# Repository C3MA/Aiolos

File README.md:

avr-template
============

A minimal template for AVR microcontroller projects. Usage:

1. Fork this repository, then rename it to reflect your project
(Admin->Rename on Github)
2. Clone your repository
3. Change the Makefile to reflect your microcontroller, programmer etc.

### License

The UART code is written by Peter Fleury. Everything else: BSD 2-clause
license as below:

Copyright (c) 2012, Mathias Dalheimer
All rights reserved.

Redistribution and use in source and binary forms, with or without
modification, are permitted provided that the following conditions are
met:

* Redistributions of source code must retain the above copyright notice, 
this list of conditions and the following disclaimer.

* Redistributions in binary form must reproduce the above copyright
notice, this list of conditions and the following disclaimer in the
documentation and/or other materials provided with the distribution.

THIS SOFTWARE IS PROVIDED BY THE COPYRIGHT HOLDERS AND CONTRIBUTORS "AS
IS" AND ANY EXPRESS OR IMPLIED WARRANTIES, INCLUDING, BUT NOT LIMITED
TO, THE IMPLIED WARRANTIES OF MERCHANTABILITY AND FITNESS FOR A
PARTICULAR PURPOSE ARE DISCLAIMED. IN NO EVENT SHALL THE COPYRIGHT
HOLDER OR CONTRIBUTORS BE LIABLE FOR ANY DIRECT, INDIRECT, INCIDENTAL,
SPECIAL, EXEMPLARY, OR CONSEQUENTIAL DAMAGES (INCLUDING, BUT NOT
LIMITED TO, PROCUREMENT OF SUBSTITUTE GOODS OR SERVICES; LOSS
OF USE, DATA, OR PROFITS; OR BUSINESS INTERRUPTION) HOWEVER
CAUSED AND ON ANY THEORY OF LIABILITY, WHETHER IN CONTRACT,
STRICT LIABILITY, OR TORT (INCLUDING NEGLIGENCE OR OTHERWISE)
ARISING IN ANY WAY OUT OF THE USE OF THIS SOFTWARE, EVEN IF ADVISED OF
THE POSSIBILITY OF SUCH DAMAGE.

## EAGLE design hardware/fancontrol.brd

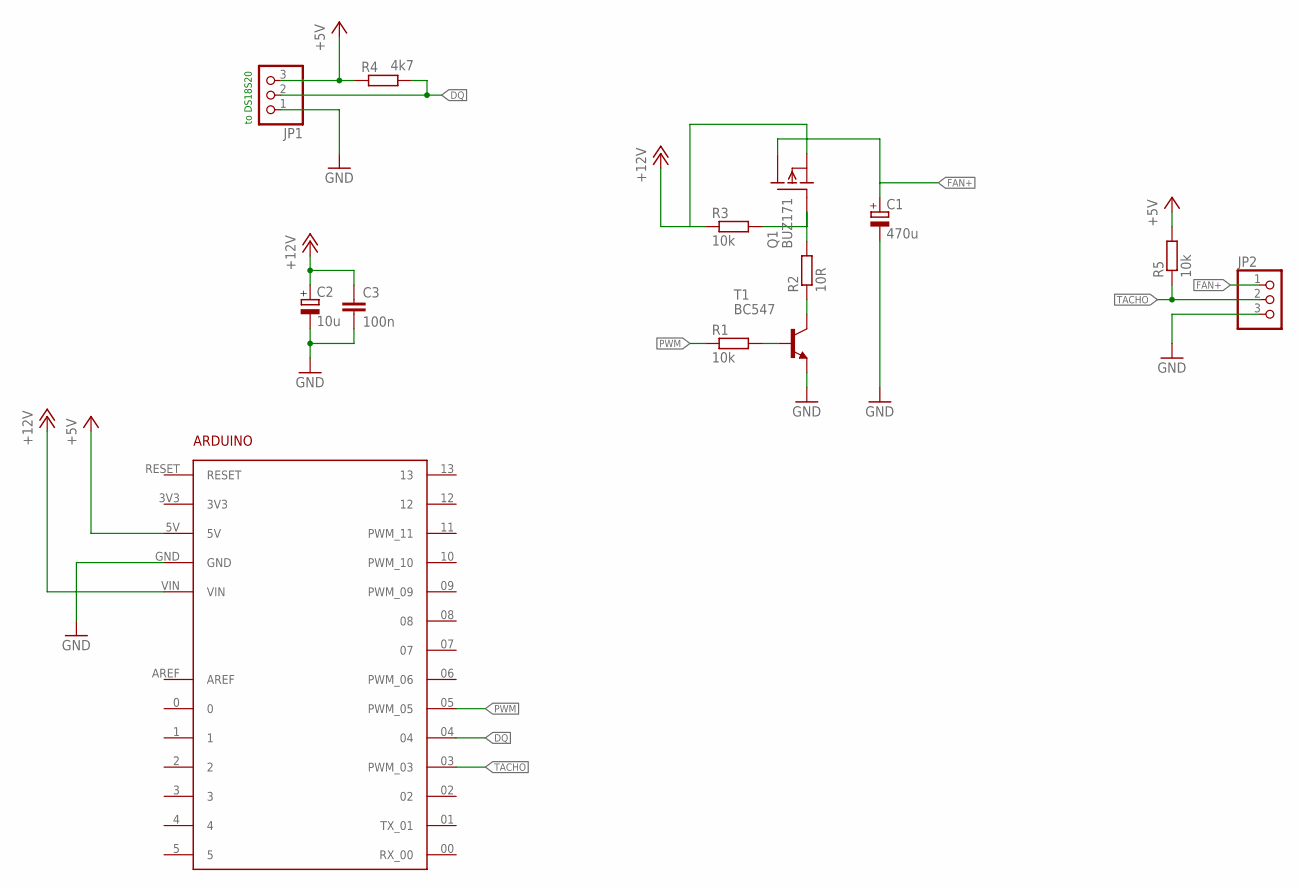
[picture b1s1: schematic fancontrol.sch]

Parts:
ARDUINO1: ARDUINO
C1: 470u; E5-10,5
C2: 10u; E2,5-5
C3: 100n; C025-025X050
JP1, JP2: PINHD-1X3; 1X03
Q1: BUZ171; TO220
R1, R3, R5: 10k; 0207/7
R2: 10R; 0207/7
R4: 4k7; 0207/7
T1: BC547; TO92

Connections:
+5V: ARDUINO1.5V, JP1.3, R4.1, R5.2
+12V: ARDUINO1.VIN, C2.+, C3.1, Q1.3 (S), R3.1
DQ: ARDUINO1.04, JP1.2, R4.2
FAN+: C1.+, JP2.1, Q1.2 (D)
GND: ARDUINO1.GND, C1.-, C2.-, C3.2, JP1.1, JP2.3, T1.1 (E)
unnamed: R1.2, T1.2 (B)
unnamed: R2.1, T1.3 (C)
unnamed: Q1.1 (G), R2.2, R3.2
PWM: ARDUINO1.05 (PWM_05), R1.1
TACHO: ARDUINO1.03 (PWM_03), JP2.2, R5.1

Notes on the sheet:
to DS18S20

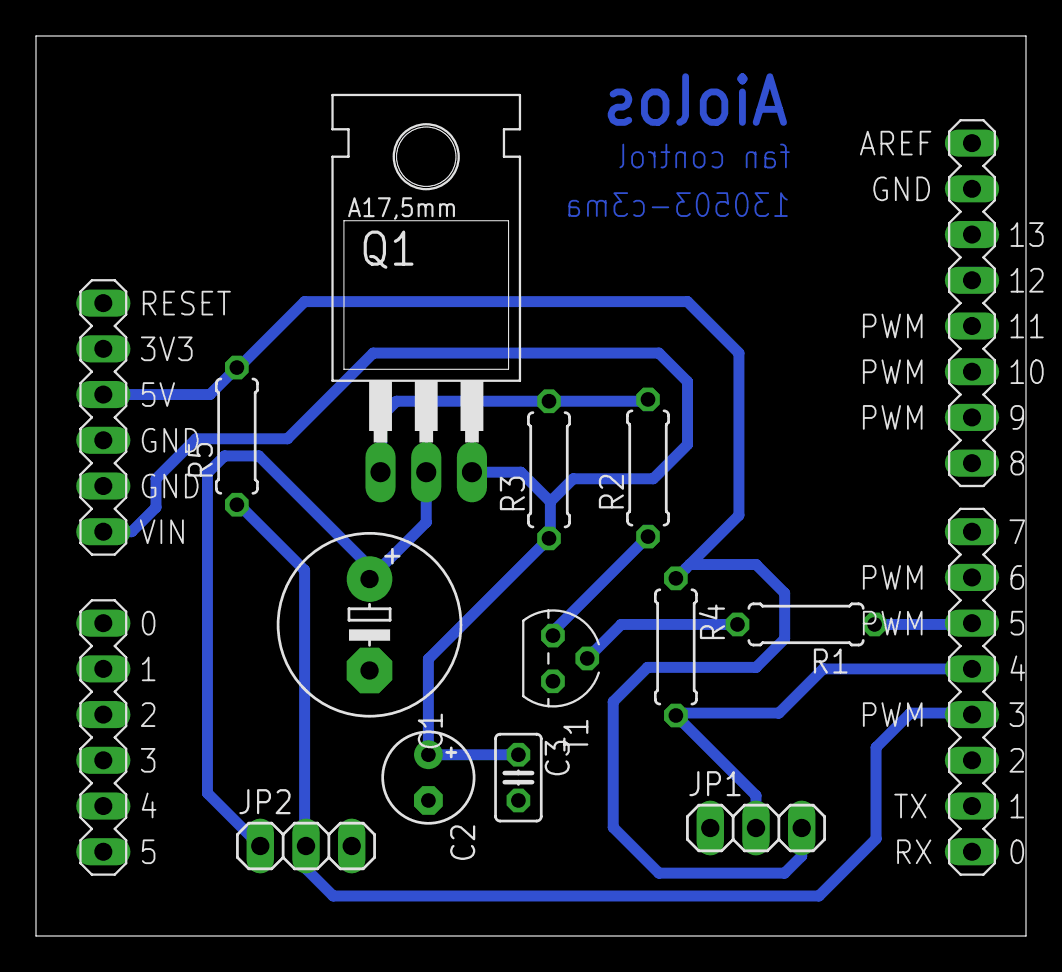
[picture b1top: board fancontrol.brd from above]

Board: 2 copper layers, 55.0 x 50.0 mm, 13 parts (0 on the bottom side), 10 nets.

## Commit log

2012-11-20 added usage note
2013-01-27 first prototype firmware for the temperature control of der Schrank
2013-01-27 Ignore eagle temp files
2013-01-27 empty schematic
2013-01-27 fan control
2013-01-27 generated board
2013-01-27 populated the pcb
2013-01-27 finished the routung
2013-01-27 added version number
2013-01-27 added PDFs of sch and brd
2013-01-27 changed R2 from 10k to 10R
2013-02-19 Update limits
2013-02-20 restored .gitignore
2013-02-20 connect JP2 to GND. Fixes #2
2013-02-20 added capacitors to Vin. Fixes #1
2013-02-24 New electronic
    Changed the electronic design. Now only a transistor is needed, instead
    of transistor and modfet.
2013-02-24 New pcb layout
    + new pdf files.
2013-04-28 Added Tachosignal and PID
2013-05-03 Replace transistor, make routes wider
2013-05-03 Fix one wire to make GND work again
